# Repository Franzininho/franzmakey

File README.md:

# FranzMakey

FRANZmakey é um kit com funcionamento similar ao Makey Makey, porém com um custo bem mais acessível e é feito no Brasil. O objetivo dessa placa é possibilitar a interação com o computador através de objetos inusitados, como: frutas, legumes, etc, e assim estimular a criatividade com muita mão na massa e o pensamento computacional através da programação no Scratch.

Placa FranzMakey

Com esse kit você pode colocar a criatividade e mão na massa para funcionar, você pode criar um controle para controlar os controlar jogos no Scartch, animar personagens no Scratch tocando em frutas, criar narrativas, fazer músicas tocando em frutas e etc.

# Documentação

[Documentação do FranzMakey](https://franzininho.github.io/docs-franzininho-site/docs/FranzMakey/franzmakey)

# Onde comprar?

Esse kit é feito sob encomenda. Para adquiri-lo, entre em contato conosco: contato@franzininho.com.br﻿

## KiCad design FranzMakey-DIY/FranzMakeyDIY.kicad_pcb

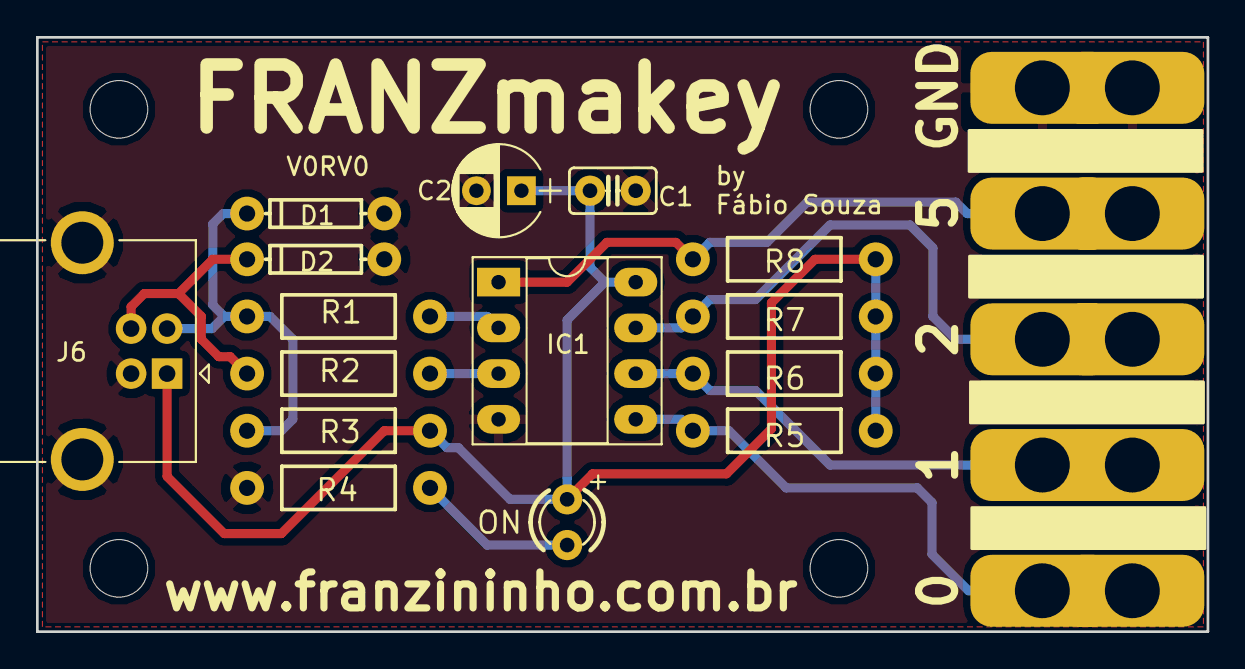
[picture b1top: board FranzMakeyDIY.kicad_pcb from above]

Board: 2 copper layers, 65.0 x 33.0 mm, 20 parts (0 on the bottom side), 11 nets.

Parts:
0, 1, 2, 5: Conn_01x01; alligator
C1: 0.1uf; C025-025X050
C2: CP; CP_Radial_D5.0mm_P2.50mm
D1, D2: BZT52; DIODE-BZT52
GND: Conn_01x01; alligator
IC1: ATTINY85 - 20PU; DIP-8_W7.62mm_Socket_LongPads
J6: USB_B; USB_B_OST_USB-B1HSxx_Horizontal
ON: LED3MM
R1, R2: 68R; AXIAL-0.4
R3: 1K5; AXIAL-0.4
R4: 1K; AXIAL-0.4
R5, R6, R7: 10M; AXIAL-0.4
R8: 10K; AXIAL-0.4

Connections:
5V: C1.1, C2.1, IC1.8, J6.1, ON.A, R3.P$1, R5.P$1, R6.P$1, R7.P$1, R8.P$1
GND: C1.2, C2.2, D1.A, D2.A, GND.1, IC1.4, J6.4, J6.5, R4.P$1
unnamed: D1.C, J6.2, R1.P$1, R3.P$2
unnamed: D2.C, J6.3, R2.P$1
unnamed: 5.1, IC1.1, R8.P$2
unnamed: IC1.2, R1.P$2
unnamed: IC1.3, R2.P$2
unnamed: 0.1, IC1.5, R5.P$2
unnamed: 1.1, IC1.6, R6.P$2
unnamed: 2.1, IC1.7, R7.P$2
unnamed: ON.K, R4.P$2

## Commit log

2021-09-28 Adicionando projeto completo
